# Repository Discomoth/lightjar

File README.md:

```
  ####                                                    ###             ##        ####                       ## 
 ##      ###   ###    ## ## ##   ###     ###   ## ##    ###     ###    ####    ###  ## ##   ###  ## #   ####   ## 
 ##     # ##  # ##    ########  # ##    ## ##  #####    ##     ## ##  ## ##   # ##  ## ##  # ##  ####  ## ##  ##  
  ##   ## ## ## ##    ## ## ## ## ##   ##  ##  ## ##   ##     ##  ## ##  ##  ## ## #####  ## ##  ##   ##  ##  ##  
   ##  ####  ####    ##  #  #  ####    ##  ## ##  #    ##     ##  ## ## ##   ####  ##  ## ####  ##    ## ##       
   ##  ##    ##      ## ## ##  ##      ## ##  ## ##    ###    ## ##  #####   ##    ##  ## ##    ##    #####  ##   
####    ###   ###    ## ## ##   ###     ###   ## ##     ####   ###   ## ##    ###  #####   ###  ##    ## ##  ##   
                                                                                                         ##       
                                                                                                      ####
```

```
                                                                                                                                                                                   
##       #   #                    #     #                 ##        ##                                               # ######    #                                      #  ##      
 #       #   #                   ##    ##                  #         #                                              ##  #    #                                          #   #      
 #       #   #                   #     #                   #         #                                              #   #     #                                         #   #      
 #####  ### ### #####  #### #    #     #   ####  ####   ####   ###   ####   ###  ####  ####     ####  ####  ####    #   #     # ##  ####  ####  ####  ########   ####  ###  #####  
 #   #   #   #   #   # #  #     #     #   #   # ##  ## #   #  #   #  #   # #   #  # # #  #     ##  ##  # # #  #    #    #     #  #  #  # #   # ##  ##  #  #  #  ##  ##  #   #   #  
 #   #   #   #   #   #  ##      #     #   #     #    # #   #  #####  #   # #####  #   #  #     #    #  #   #  #    #    #     #  #   ##  #     #    #  #  #  #  #    #  #   #   #  
 #   #   #   #   #   # #  #    #     #    ##    ##  ## #   #  #      #   # #      #    ##      ##  ##  #    ##    #     #    #   #  #  # ##    ##  ##  #  #  #  ##  ##  #   #   #  
### ###  ##  ##  ####  #### #  #     #     ####  ####   #####  ####  ####   #### ###  ##### ##  ####  ###  #####  #    ######   ### ####  ####  ####  #########  ####   ## ### ### 
                 #            ##    ##                                                #   #                #   # ##                                                                
                ###           #     #                                                 ####                 ####  #                                                                 
```

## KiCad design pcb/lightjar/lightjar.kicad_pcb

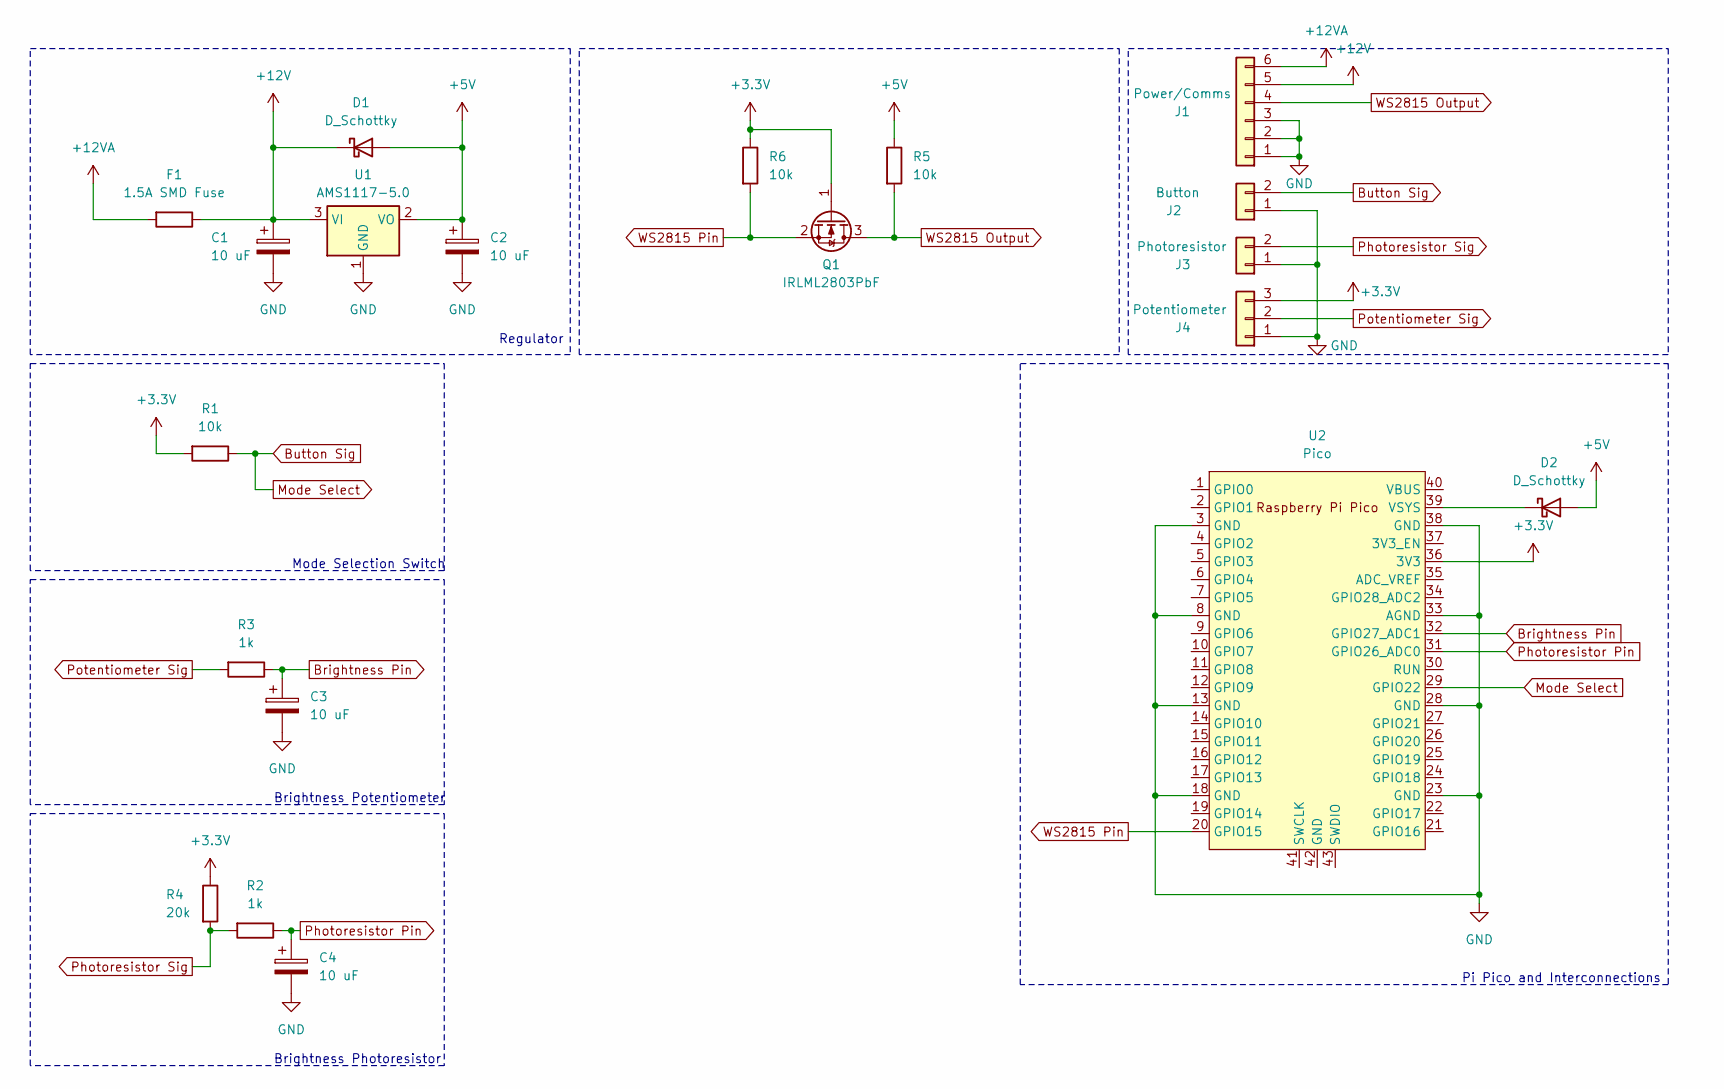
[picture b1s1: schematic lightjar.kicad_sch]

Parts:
C1, C2, C3, C4: 10 uF; R_1206_3216Metric_Pad1.30x1.75mm_HandSolder
D1, D2: D_Schottky; D_SOD-123
F1: 1.5A SMD Fuse; R_1206_3216Metric_Pad1.30x1.75mm_HandSolder
J1: Power/Comms; TerminalBlock_Phoenix_PT-1,5-6-3.5-H_1x06_P3.50mm_Horizontal
J2: Button; TerminalBlock_Phoenix_PT-1,5-2-3.5-H_1x02_P3.50mm_Horizontal
J3: Photoresistor; TerminalBlock_Phoenix_PT-1,5-2-3.5-H_1x02_P3.50mm_Horizontal
J4: Potentiometer; TerminalBlock_Phoenix_PT-1,5-3-3.5-H_1x03_P3.50mm_Horizontal
Q1: IRLML2803PbF; SOT-23
R1, R5, R6: 10k; R_0603_1608Metric_Pad0.98x0.95mm_HandSolder
R2, R3: 1k; R_0603_1608Metric_Pad0.98x0.95mm_HandSolder
R4: 20k; R_0603_1608Metric_Pad0.98x0.95mm_HandSolder
U1: AMS1117-5.0; SOT-223-3_TabPin2
U2: Pico; RPi_Pico_SMD_TH

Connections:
+3.3V: J4.3, Q1.1 (G), R1.2, R4.1, R6.1, U2.36 (3V3)
+5V: C2.1, D1.2 (A), D2.2 (A), R5.1, U1.2 (VO)
+12V: C1.1, D1.1 (K), F1.1, J1.5, U1.3 (VI)
+12VA: F1.2, J1.6
Brightness Pin: C3.1, R3.1, U2.32 (GPIO27_ADC1)
Button Sig: J2.2, R1.1, U2.29 (GPIO22)
GND: C1.2, C2.2, C3.2, C4.2, J1.1, J1.2, J1.3, J2.1, J3.1, J4.1, U1.1 (GND), U2.3 (GND), U2.8 (GND), U2.13 (GND), U2.18 (GND), U2.23 (GND), U2.28 (GND), U2.33 (AGND), U2.38 (GND)
unnamed: D2.1 (K), U2.39 (VSYS)
Photoresistor Pin: C4.1, R2.1, U2.31 (GPIO26_ADC0)
Photoresistor Sig: J3.2, R2.2, R4.2
Potentiometer Sig: J4.2, R3.2
WS2815 Output: J1.4, Q1.3 (D), R5.2
WS2815 Pin: Q1.2 (S), R6.2, U2.20 (GPIO15)

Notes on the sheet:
Regulator
Brightness Photoresistor
Brightness Potentiometer
Pi Pico and Interconnections
Mode Selection Switch

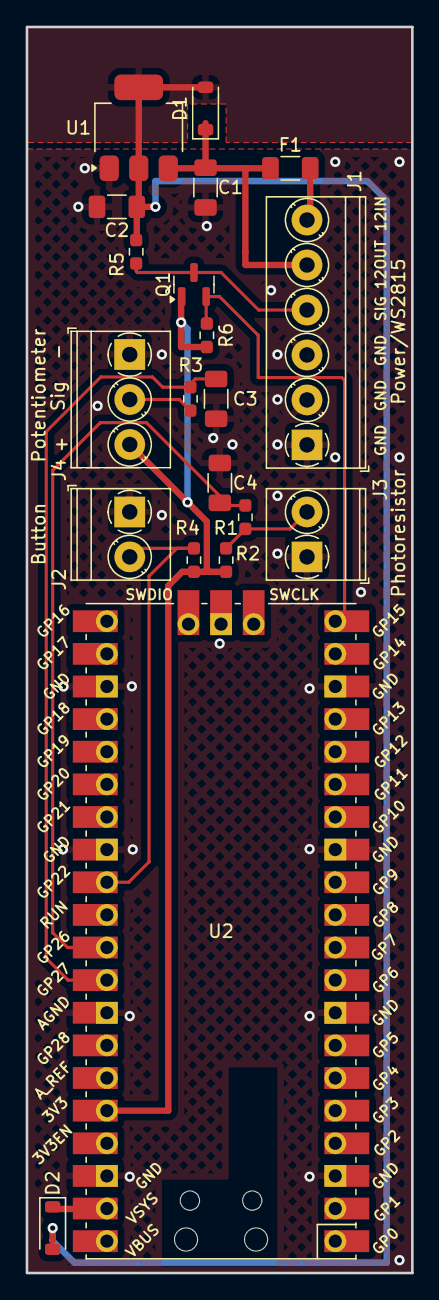
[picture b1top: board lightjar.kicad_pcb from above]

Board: 2 copper layers, 30.0 x 97.0 mm, 20 parts (0 on the bottom side), 13 nets.

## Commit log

2024-12-02 Schematic and PCB creation
2024-12-03 LED order remapping
2024-12-03 Hex-to-rgb conversion function
2024-12-03 Added LED reset function
2024-12-03 Added additional LED sequences
2024-12-03 Added palettes file and import
2024-12-03 LED sequence simulator initial commit
2024-12-03 Added 4x base print file.
2024-12-03 Implemented color_dict and color interpolation. Saving those rams.
2024-12-03 Updated sweeping_colors to use interpolation
2024-12-03 Changed sweeping color timing parameters
2024-12-03 Updated palettes.py to have interpolation start and stop information
2024-12-03 Updated simulator to reflect interpolation changes in main.py
2024-12-03 Palette generator construction and initial commit
2024-12-05 Added ocean_waves sequence
2024-12-13 Layout and schematic updates
2024-12-13 Structure and coverplate updates.
2024-12-13 Propaganda generation.
2024-12-15 Change to segmented gradient generation. Tab reformatting.
2024-12-15 Tab reformatting
2024-12-15 Color chase animation
2024-12-15 Added cycle animation
2024-12-15 Added rotator animation
2024-12-15 Added flame animation
2024-12-15 Added lid variants, STLs and 3MF files.
2024-12-21 Pretty much rewriting everything to get final code ready!
2024-12-23 The final bastardization to get things finally functional... ;)
2024-12-25 Fixed silly goof with palette list length.
2024-12-25 Created deploy-able UF2 format firmware image!~
2024-12-25 Added an indicator toggle function to show device is functioning.
2024-12-25 Update firmware binary, add debug build with watchdog bypass.
2024-12-25 Added readme.
2024-12-25 eric7 project file update
2024-12-25 README heading fix
2025-06-15 A04 lid design
2025-06-28 Changed submodule update and debug firmware steps.
2025-06-28 Whitespace removal
2025-06-28 Added potentiometer input when in automatic brightness mode.
2025-06-28 Re-compiled firmware distribution for potentiometer input in automatic mode.
2025-07-13 Change to rounded design
2025-07-13 Update to FET driver design
2025-08-12 See ya!
